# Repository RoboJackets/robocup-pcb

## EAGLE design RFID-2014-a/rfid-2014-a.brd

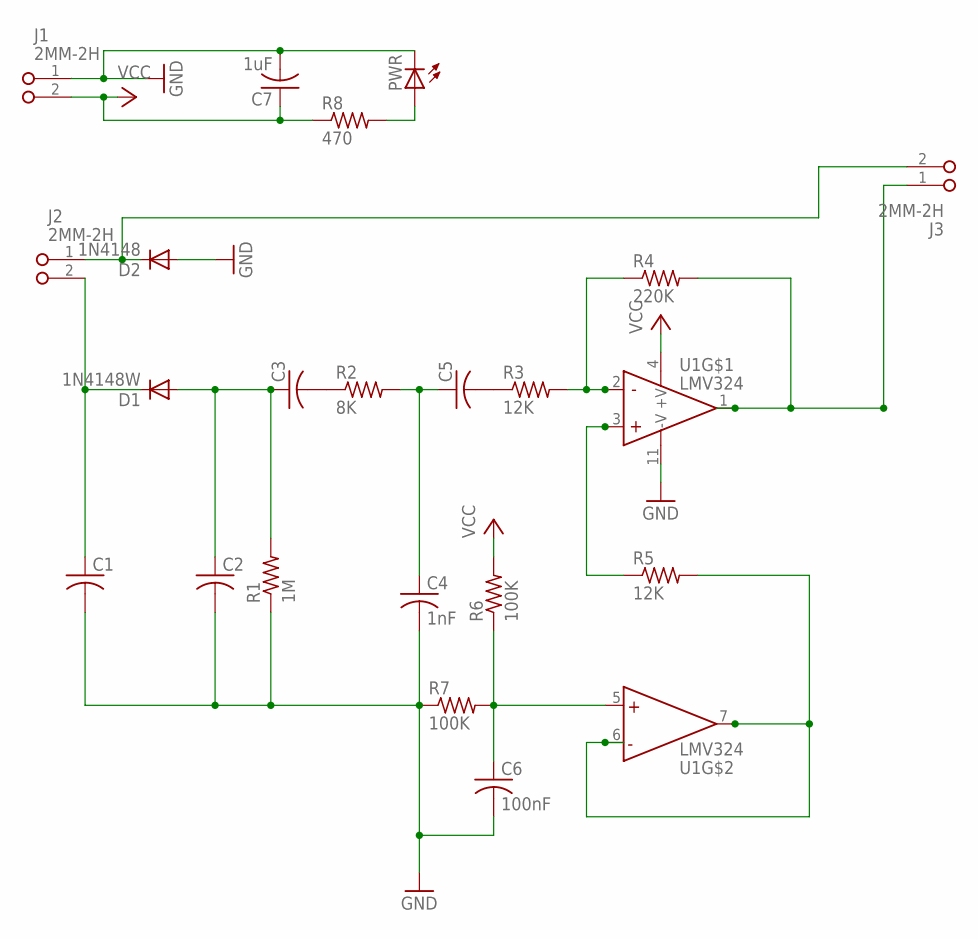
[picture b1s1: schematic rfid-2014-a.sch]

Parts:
C1, C2, C3, C5: C-USC0603; C0603
C4: 1nF; C0603
C6: 100nF; C0603
C7: 1uF; C0603
D1: 1N4148W; SOD123
D2: 1N4148; SOD123
J1, J2, J3: 2MM-2H; 2MM-2-H
PWR: LEDCHIPLED_0603; CHIPLED_0603
R1: 1M; R0603
R2: 8K; R0603
R3, R5: 12K; R0603
R4: 220K; R0603
R6, R7: 100K; R0603
R8: 470; R0603
U1: LMV324; SO014

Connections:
+IN: U1.10 (+IN), U1.12 (+IN)
-IN: U1.9 (-IN), U1.13 (-IN)
GND: C1.2, C2.2, C4.2, C6.2, C7.2, D2.A, J1.1, PWR.C, R1.1, R7.1, U1.11 (-V)
unnamed: R3.2, R4.1, U1.2 (-IN)
unnamed: J3.1, R4.2, U1.1 (OUT)
unnamed: C3.2, R2.1
unnamed: R5.1, U1.3 (+IN)
unnamed: R5.2, U1.6 (-IN), U1.7 (OUT)
unnamed: C5.2, R3.1
unnamed: C6.1, R6.1, R7.2, U1.5 (+IN)
unnamed: C4.1, C5.1, R2.2
unnamed: C1.1, D1.C, J2.2
unnamed: C2.1, C3.1, D1.A, R1.2
unnamed: D2.C, J2.1, J3.2
unnamed: PWR.A, R8.2
OUT: U1.8 (OUT), U1.14 (OUT)
VCC: C7.1, J1.2, R6.2, R8.1, U1.4 (+V)

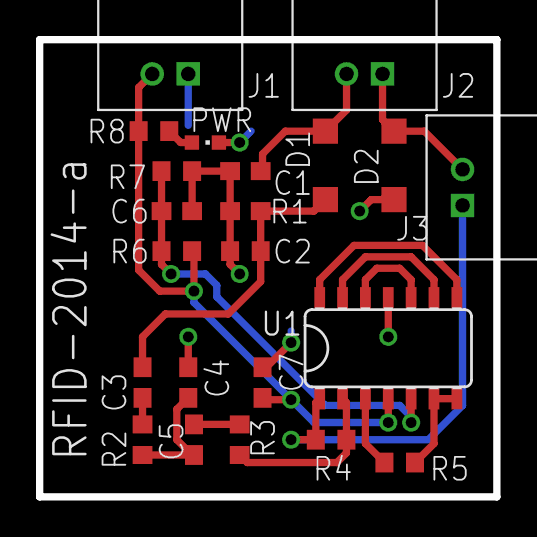
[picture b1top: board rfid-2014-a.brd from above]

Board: 2 copper layers, 25.4 x 25.4 mm, 22 parts (0 on the bottom side), 17 nets.

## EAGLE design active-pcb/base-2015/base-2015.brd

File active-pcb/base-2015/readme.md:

# Radio Board 2015

The 2015 radio has an mbed as the main processor and two radio boards.  We currently only use one of them, but in the future we'd like to support more than six robots at a time.  Two radio boards should give us capacity to communicate with 12 if we implement it in software.

The board also has a mini usb connector, which is used in normal operation.  The mbed's usb port is only needed for flashing new firmware or debugging.  You can use the two usb ports simultaneously.

## PCB

* Radio board connector: "CONN HEADER 10POS .050 VERT SMD"
  * http://www.digikey.com/product-search/en/connectors-interconnects/rectangular-board-to-board-connectors-headers-male-pins/1442672?k=609%203175%20nd

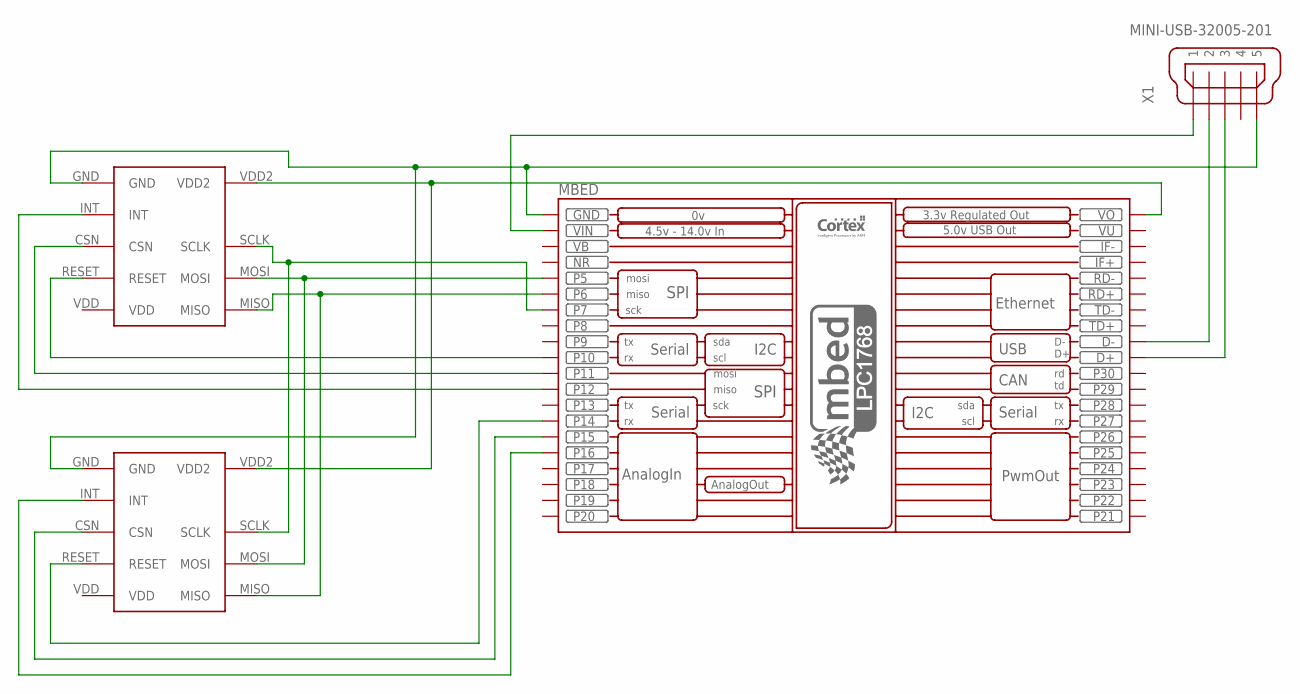
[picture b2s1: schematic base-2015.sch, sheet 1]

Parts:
MBED: MBED_NXP_LPC1768; MBED-KIT
U$1, U$2: RADIOBOARD2015CONNECTOR
X1: MINI-USB-32005-201; 32005-201

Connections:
unnamed: MBED.P$5 (P5), U$1.MOSI, U$2.MOSI
unnamed: MBED.P$6 (P6), U$1.MISO, U$2.MISO
unnamed: MBED.P$15 (P15), U$2.CSN
unnamed: MBED.VIN, X1.1
unnamed: MBED.D-, X1.2
unnamed: MBED.D+, X1.3
unnamed: MBED.VOUT (VO), U$1.VDD2, U$2.VDD2
unnamed: MBED.P$12 (P12), U$1.INT
unnamed: MBED.P$11 (P11), U$1.CSN
unnamed: MBED.P$10 (P10), U$1.RESET
unnamed: MBED.P$16 (P16), U$2.INT
unnamed: MBED.P$14 (P14), U$2.RESET
unnamed: MBED.GND, U$1.GND, U$2.GND, X1.5
unnamed: MBED.P$7 (P7), U$1.SCLK, U$2.SCLK
VB: MBED.VB
VU: MBED.VU

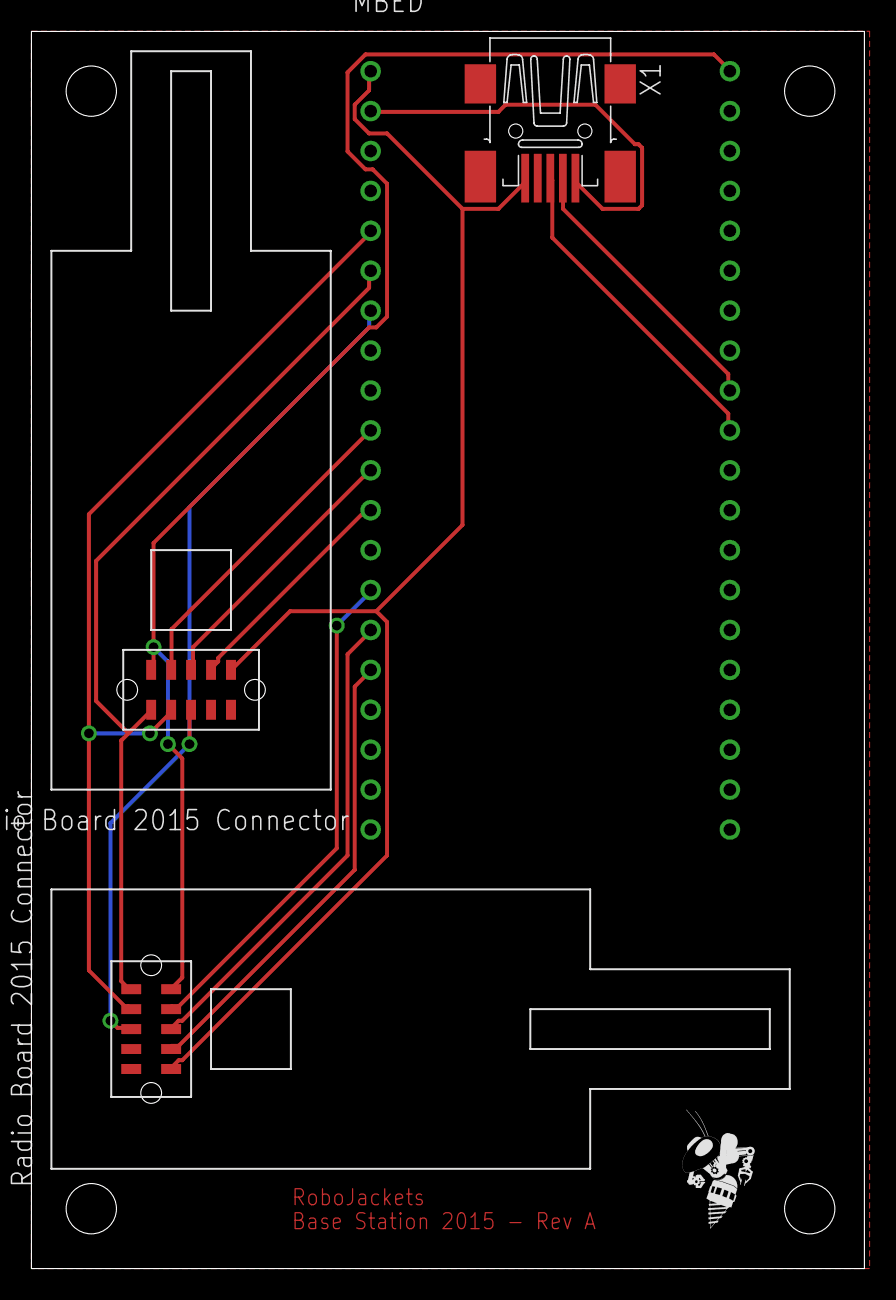
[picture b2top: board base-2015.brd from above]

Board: 2 copper layers, 53.0 x 78.7 mm, 5 parts (0 on the bottom side), 14 nets.

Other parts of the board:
U$3: ROBOBUZZ0.4X; ROBOBUZZ_0.4X

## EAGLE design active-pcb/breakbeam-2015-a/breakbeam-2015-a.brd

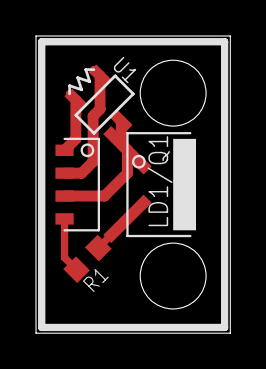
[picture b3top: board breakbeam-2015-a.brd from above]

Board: 2 copper layers, 10.8 x 16.5 mm, 5 parts (0 on the bottom side), 5 nets.

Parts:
LD1/Q1: 2LEAD_H_FACEDOWN_SHORT_MIN
R1: R0603
R3: 0.3k-2.2k; GHOST_0.075
U1: SOT-23-3
U$1: PAD_4

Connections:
+5V: R3.P$2, U1.2, U$1.P$1
GND: LD1/Q1.1, U1.3, U$1.P$3
unnamed: LD1/Q1.2, R1.2
OPTICAL: R1.1, U$1.P$4
SERIAL_ID: R3.P$1, U1.1, U$1.P$2

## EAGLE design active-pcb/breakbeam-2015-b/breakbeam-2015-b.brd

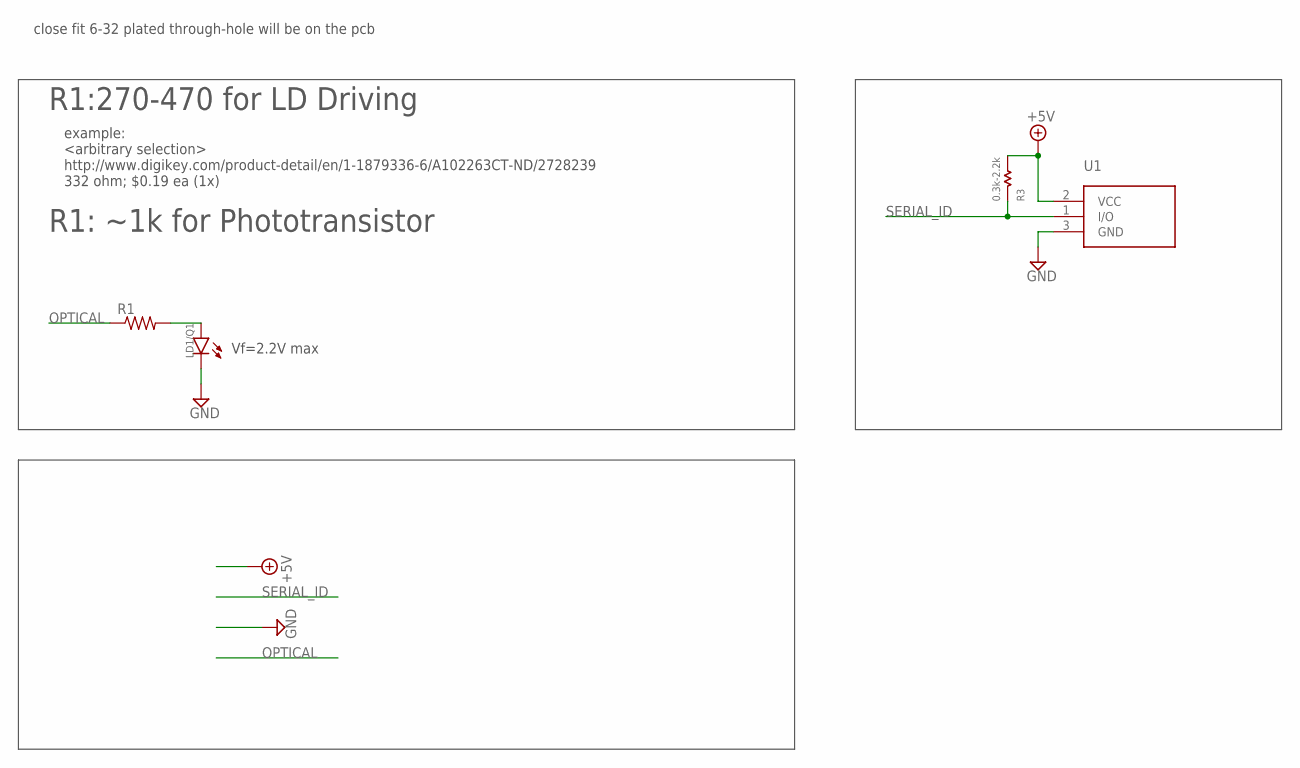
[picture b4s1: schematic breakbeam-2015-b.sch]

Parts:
LD1/Q1: LD_SIDELOOK_FACEDOWNEXTRA_SHORT_LEAD_MINIMIZED; 2LEAD_H_FACEDOWN_XSHORT_MIN
R1: R-US_R0603; R0603
R3: 0.3k-2.2k; GHOST_0.075
U1: DS2411; SOT-23-3

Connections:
+5V: R3.P$2 (PIN2), U1.2 (VCC)
GND: LD1/Q1.1 (C), U1.3 (GND)
unnamed: LD1/Q1.2 (A), R1.2
OPTICAL: R1.1
SERIAL_ID: R3.P$1 (PIN1), U1.1 (I/O)

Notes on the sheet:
Vf=2.2V max
example: <arbitrary selection> http://www.digikey.com/product-detail/en/1-1879336-6/A102263CT-ND/2728239 332 ohm; $0.19 ea (1x)
close fit 6-32 plated through-hole will be on the pcb
R1:270-470 for LD Driving
R1: ~1k for Phototransistor

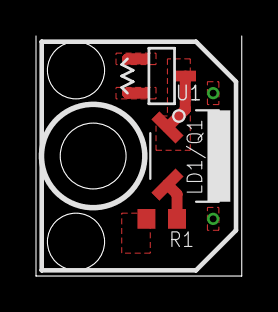
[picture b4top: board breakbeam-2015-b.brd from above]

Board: 2 copper layers, 11.4 x 13.3 mm, 4 parts (0 on the bottom side), 4 nets.

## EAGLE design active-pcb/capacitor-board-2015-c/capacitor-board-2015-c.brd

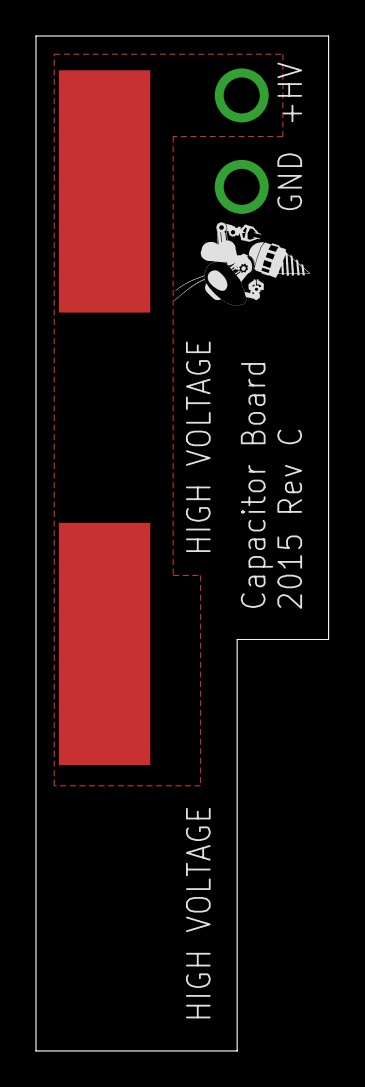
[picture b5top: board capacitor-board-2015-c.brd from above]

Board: 2 copper layers, 16.3 x 56.4 mm, 6 parts (1 on the bottom side), 2 nets, no tracks yet.

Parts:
C1, C2: 25MM-DIA_HORIZ
U$1, U$3: VIA_2MM
U$2, U$4: ROBOBUZZ_0.4X

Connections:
GND: C1.-, C2.-, U$3.P$1
HV: C1.+, C2.+, U$1.P$1

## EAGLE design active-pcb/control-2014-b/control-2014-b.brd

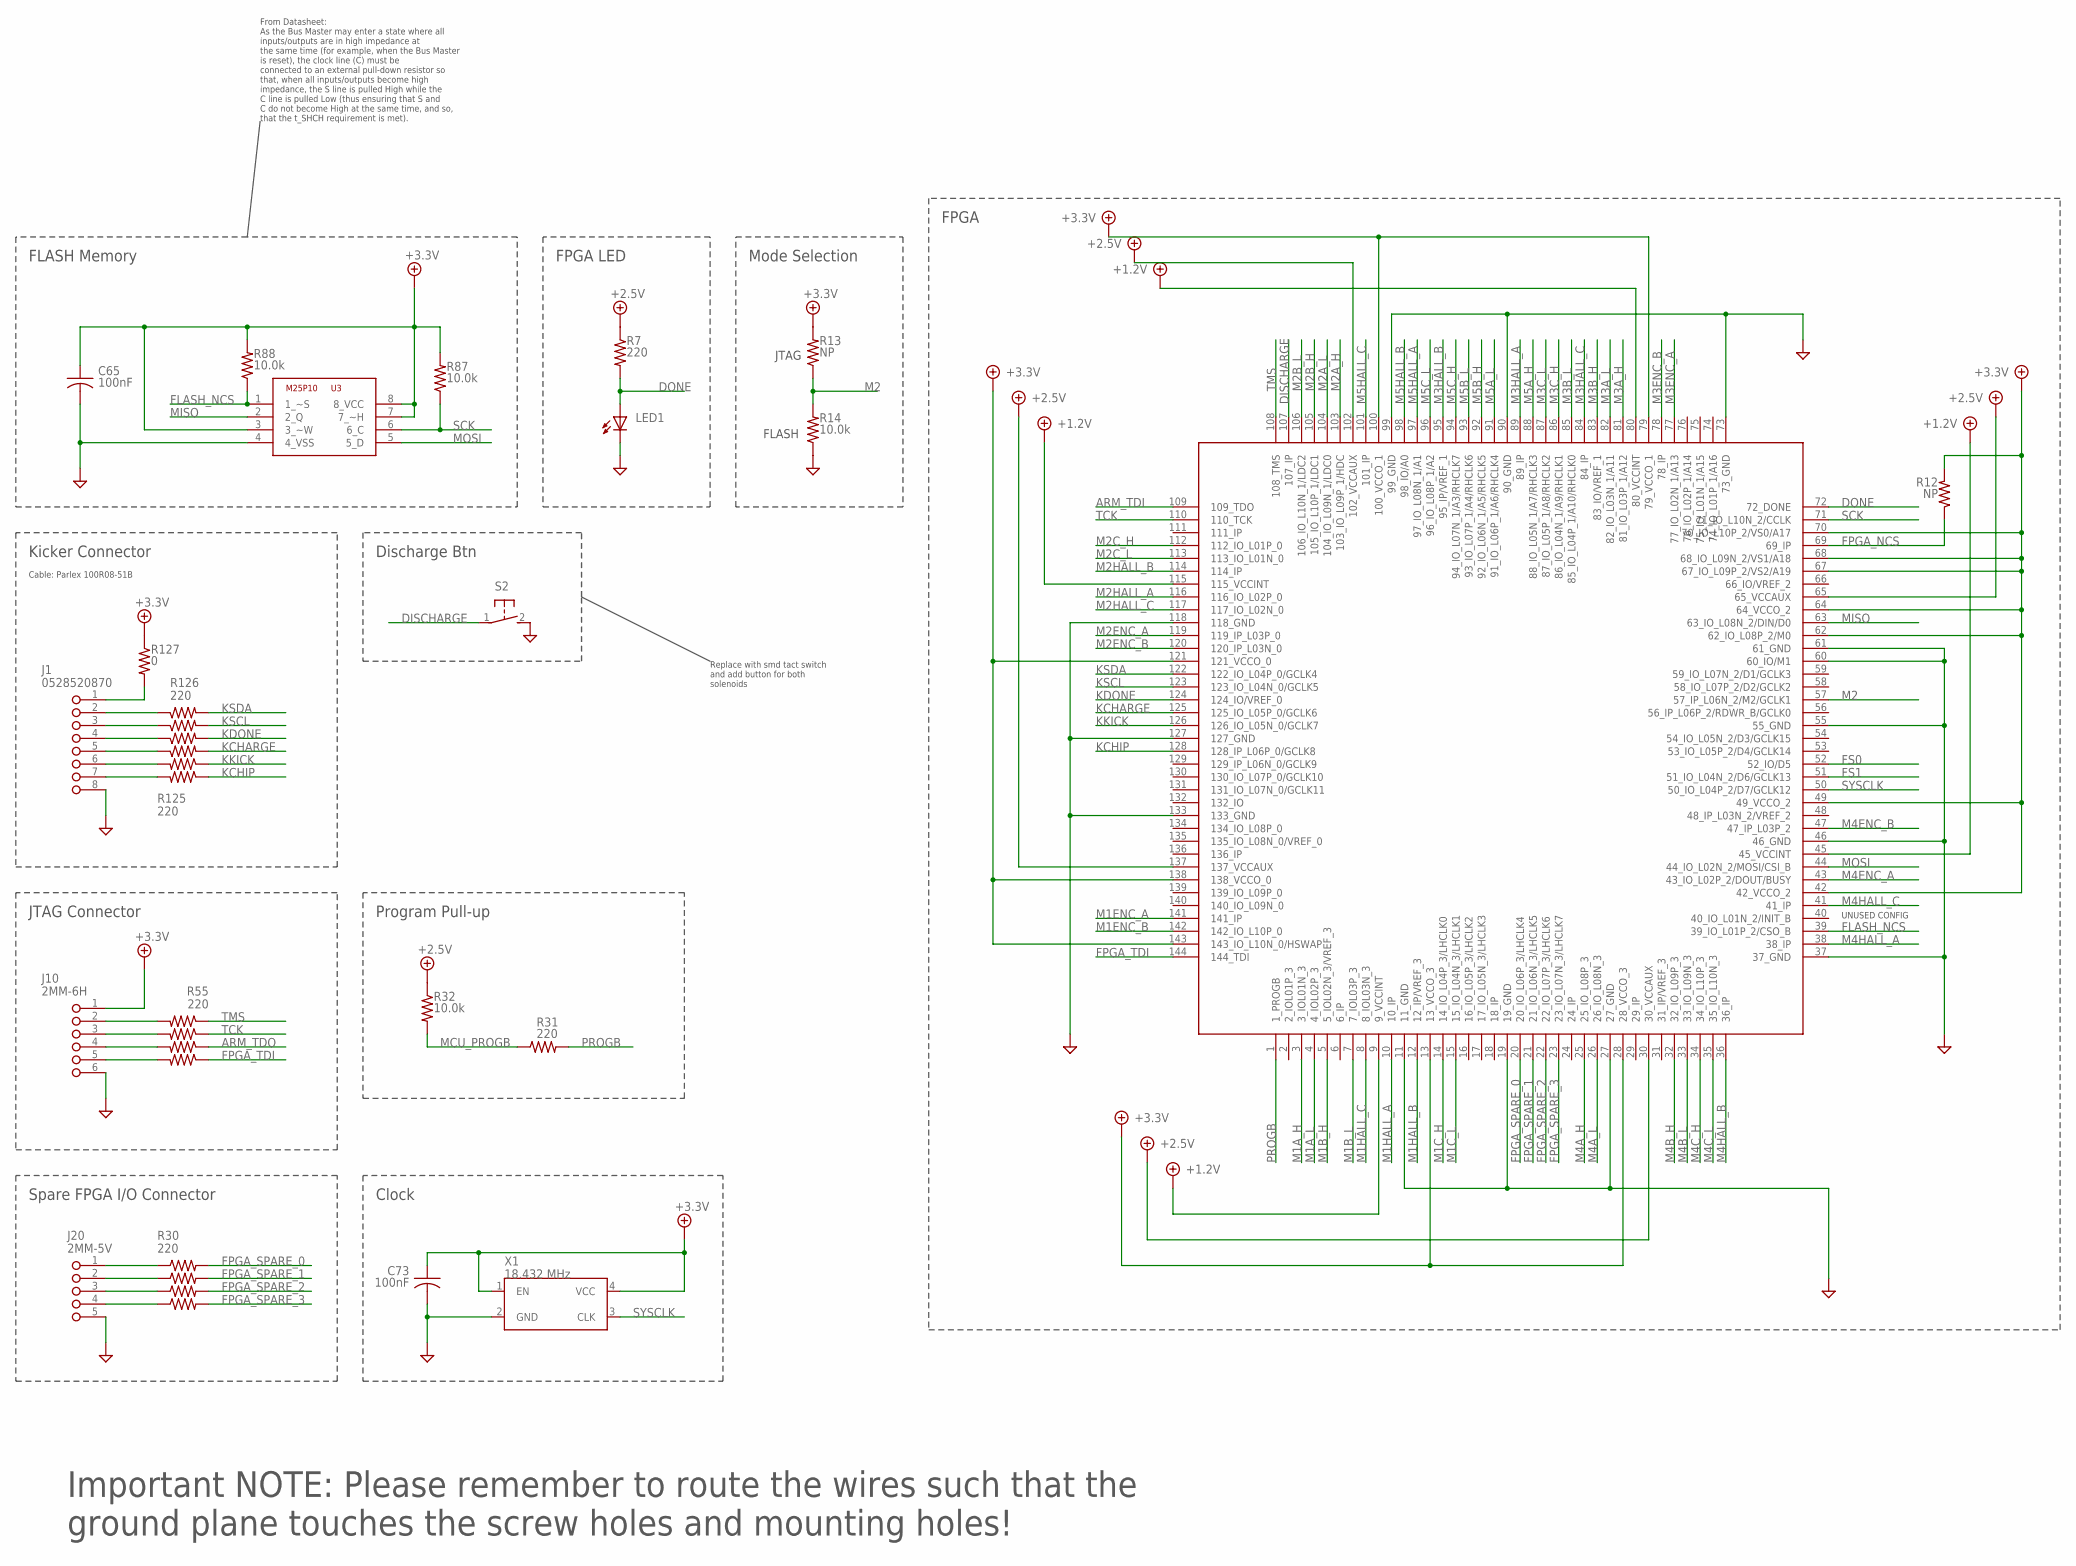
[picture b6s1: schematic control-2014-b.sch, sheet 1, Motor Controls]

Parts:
C65, C73: 100nF; C0603
J1: 0528520870
J10: 2MM-6H; 2MM-6-H
J20: 2MM-5V; 2MM-5-V
LED1: LEDCHIP-LED0603; CHIP-LED0603
R7, R31: 220; R0603
R12, R13: NP; R0603
R14, R32, R87, R88: 10.0k; R0603
R30, R55, R126: 220; RA_4_1206
R125: 220; RA_2_0606
R127: 0; R0603
S2: 31-XX; B3F-31XX
U1: XC3S100E; TQFP144
U3: M25P10; SO08
X1: 18.432 MHz; XTAL_LCC

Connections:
+1.2V: U1.9 (9_VCCINT), U1.45 (45_VCCINT), U1.80 (80_VCCINT), U1.115 (115_VCCINT); also elsewhere on the board
+2.5V: R7.1, R32.1, U1.30 (30_VCCAUX), U1.65 (65_VCCAUX), U1.102 (102_VCCAUX), U1.137 (137_VCCAUX); also elsewhere on the board
+3.3V: C65.1, C73.1, J10.1, R12.2, R13.2, R87.2, R88.2, R127.1, U1.13 (13_VCCO_3), U1.28 (28_VCCO_3), U1.42 (42_VCCO_2), U1.49 (49_VCCO_2), U1.62 (62_IO_L08P_2/M0), U1.64 (64_VCCO_2), U1.67 (67_IO_L09P_2/VS2/A19), U1.68 (68_IO_L09N_2/VS1/A18), U1.70 (70_IO_L10P_2/VS0/A17), U1.79 (79_VCCO_1), U1.100 (100_VCCO_1), U1.121 (121_VCCO_0), U1.138 (138_VCCO_0), U1.143 (143_IO_L10N_0/HSWAP), U3.3 (3_~W), U3.7 (7_~H), U3.8 (8_VCC), X1.1 (EN), X1.4 (VCC); also elsewhere on the board
ARM_TDI: U1.109 (109_TDO); also elsewhere on the board
ARM_TDO: R55.5; also elsewhere on the board
DISCHARGE: S2.1, U1.107 (107_IP)
DONE: LED1.A, R7.2, U1.72 (72_DONE)
FLASH_NCS: R88.1, U1.39 (39_IO_L01P_2/CSO_B), U3.1 (1_~S); also elsewhere on the board
FPGA_NCS: R12.1, U1.69 (69_IP); also elsewhere on the board
FPGA_SPARE_0: R30.2, U1.20 (20_IO_L06P_3/LHCLK4)
FPGA_SPARE_1: R30.4, U1.21 (21_IO_L06N_3/LHCLK5)
FPGA_SPARE_2: R30.6, U1.22 (22_IO_L07P_3/LHCLK6)
FPGA_SPARE_3: R30.8, U1.23 (23_IO_L07N_3/LHCLK7)
FPGA_TDI: R55.7, U1.144 (144_TDI)
FS0: U1.52 (52_IO/D5); also elsewhere on the board
FS1: U1.51 (51_IO_L04N_2/D6/GCLK13); also elsewhere on the board
GND: C65.2, C73.2, J1.8, J10.6, J20.5, LED1.C, R14.1, S2.2 (S), U1.11 (11_GND), U1.19 (19_GND), U1.27 (27_GND), U1.37 (37_GND), U1.46 (46_GND), U1.55 (55_GND), U1.60 (60_IO/M1), U1.61 (61_GND), U1.73 (73_GND), U1.90 (90_GND), U1.99 (99_GND), U1.118 (118_GND), U1.127 (127_GND), U1.133 (133_GND), U3.4 (4_VSS), X1.2 (GND); also elsewhere on the board
KCHARGE: R126.2, U1.125 (125_IO_L05P_0/GCLK6)
KCHIP: R125.3, U1.128 (128_IP_L06P_0/GCLK8)
KDONE: R126.4, U1.124 (124_IO/VREF_0)
KKICK: R125.1, U1.126 (126_IO_L05N_0/GCLK7)
KSCL: R126.6, U1.123 (123_IO_L04N_0/GCLK5)
KSDA: R126.8, U1.122 (122_IO_L04P_0/GCLK4)
M1A_H: U1.3 (3_IOL01N_3); also elsewhere on the board
M1A_L: U1.4 (4_IOL02P_3); also elsewhere on the board
M1B_H: U1.5 (5_IOL02N_3/VREF_3); also elsewhere on the board
M1B_L: U1.7 (7_IOL03P_3); also elsewhere on the board
M1C_H: U1.14 (14_IO_L04P_3/LHCLK0); also elsewhere on the board
M1C_L: U1.15 (15_IO_L04N_3/LHCLK1); also elsewhere on the board
M1ENC_A: U1.141 (141_IP); also elsewhere on the board
M1ENC_B: U1.142 (142_IO_L10P_0); also elsewhere on the board
M1HALL_A: U1.10 (10_IP); also elsewhere on the board
M1HALL_B: U1.12 (12_IP/VREF_3); also elsewhere on the board
M1HALL_C: U1.8 (8_IOL03N_3); also elsewhere on the board
M2: R13.1, R14.2, U1.57 (57_IP_L06N_2/M2/GCLK1)
M2A_H: U1.103 (103_IO_L09P_1/HDC); also elsewhere on the board
M2A_L: U1.104 (104_IO_L09N_1/LDC0); also elsewhere on the board
M2B_H: U1.105 (105_IO_L10P_1/LDC1); also elsewhere on the board
M2B_L: U1.106 (106_IO_L10N_1/LDC2); also elsewhere on the board
M2C_H: U1.112 (112_IO_L01P_0); also elsewhere on the board
M2C_L: U1.113 (113_IO_L01N_0); also elsewhere on the board
M2ENC_A: U1.119 (119_IP_L03P_0); also elsewhere on the board
M2ENC_B: U1.120 (120_IP_L03N_0); also elsewhere on the board
M2HALL_A: U1.116 (116_IO_L02P_0); also elsewhere on the board
M2HALL_B: U1.114 (114_IP); also elsewhere on the board
M2HALL_C: U1.117 (117_IO_L02N_0); also elsewhere on the board
M3A_H: U1.81 (81_IO_L03P_1/A12); also elsewhere on the board
M3A_L: U1.82 (82_IO_L03N_1/A11); also elsewhere on the board
M3B_H: U1.83 (83_IO/VREF_1); also elsewhere on the board
M3B_L: U1.85 (85_IO_L04P_1/A10/RHCLK0); also elsewhere on the board
M3C_H: U1.86 (86_IO_L04N_1/A9/RHCLK1); also elsewhere on the board
M3C_L: U1.87 (87_IO_L05P_1/A8/RHCLK2); also elsewhere on the board
M3ENC_A: U1.77 (77_IO_L02N_1/A13); also elsewhere on the board
M3ENC_B: U1.78 (78_IP); also elsewhere on the board
M3HALL_A: U1.89 (89_IP); also elsewhere on the board
M3HALL_B: U1.95 (95_IP/VREF_1); also elsewhere on the board
M3HALL_C: U1.84 (84_IP); also elsewhere on the board
M4A_H: U1.25 (25_IO_L08P_3); also elsewhere on the board
M4A_L: U1.26 (26_IO_L08N_3); also elsewhere on the board
M4B_H: U1.32 (32_IO_L09P_3); also elsewhere on the board
M4B_L: U1.33 (33_IO_L09N_3); also elsewhere on the board
M4C_H: U1.34 (34_IO_L10P_3); also elsewhere on the board
M4C_L: U1.35 (35_IO_L10N_3); also elsewhere on the board
M4ENC_A: U1.43 (43_IO_L02P_2/DOUT/BUSY); also elsewhere on the board
M4ENC_B: U1.47 (47_IP_L03P_2); also elsewhere on the board
M4HALL_A: U1.38 (38_IP); also elsewhere on the board
M4HALL_B: U1.36 (36_IP); also elsewhere on the board
M4HALL_C: U1.41 (41_IP); also elsewhere on the board
M5A_H: U1.88 (88_IO_L05N_1/A7/RHCLK3); also elsewhere on the board
M5A_L: U1.91 (91_IO_L06P_1/A6/RHCLK4); also elsewhere on the board
M5B_H: U1.92 (92_IO_L06N_1/A5/RHCLK5); also elsewhere on the board
M5B_L: U1.93 (93_IO_L07P_1/A4/RHCLK6); also elsewhere on the board
M5C_H: U1.94 (94_IO_L07N_1/A3/RHCLK7); also elsewhere on the board
M5C_L: U1.96 (96_IO_L08P_1/A2); also elsewhere on the board
M5HALL_A: U1.97 (97_IO_L08N_1/A1); also elsewhere on the board
M5HALL_B: U1.98 (98_IO/A0); also elsewhere on the board
M5HALL_C: U1.101 (101_IP); also elsewhere on the board
MCU_PROGB: R31.1, R32.2; also elsewhere on the board
MISO: U1.63 (63_IO_L08N_2/DIN/D0), U3.2 (2_Q); also elsewhere on the board
MOSI: U1.44 (44_IO_L02N_2/MOSI/CSI_B), U3.5 (5_D); also elsewhere on the board
unnamed: J10.3, R55.4
unnamed: J10.5, R55.8
unnamed: J1.2, R126.7
unnamed: J1.3, R126.5
unnamed: J1.4, R126.3
unnamed: J1.5, R126.1
unnamed: J10.4, R55.6
unnamed: J10.2, R55.2
unnamed: J1.6, R125.2
unnamed: J1.7, R125.4
unnamed: J1.1, R127.2
unnamed: J20.3, R30.5
unnamed: J20.2, R30.3
unnamed: J20.1, R30.1
unnamed: J20.4, R30.7
PROGB: R31.2, U1.1 (1_PROGB)
SCK: R87.1, U1.71 (71_IO_L10N_2/CCLK), U3.6 (6_C); also elsewhere on the board
SYSCLK: U1.50 (50_IO_L04P_2/D7/GCLK12), X1.3 (CLK); also elsewhere on the board
TCK: R55.3, U1.110 (110_TCK); also elsewhere on the board
TMS: R55.1, U1.108 (108_TMS); also elsewhere on the board

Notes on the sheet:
JTAG
FLASH
UNUSED CONFIG
Cable: Parlex 100R08-51B
Important NOTE: Please remember to route the wires such that the ground plane touches the screw holes and mounting holes!
JTAG Connector
Clock
Kicker Connector
Mode Selection
Discharge Btn
Program Pull-up
FLASH Memory
FPGA LED
FPGA
Spare FPGA I/O Connector
Replace with smd tact switch and add button for both solenoids
From Datasheet: As the Bus Master may enter a state where all inputs/outputs are in high impedance at the same time (for example, when the Bus Master is reset), the clock line (C) must be connected to an external pull-down resistor so that, when all inputs/outputs become high impedance, the S line 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

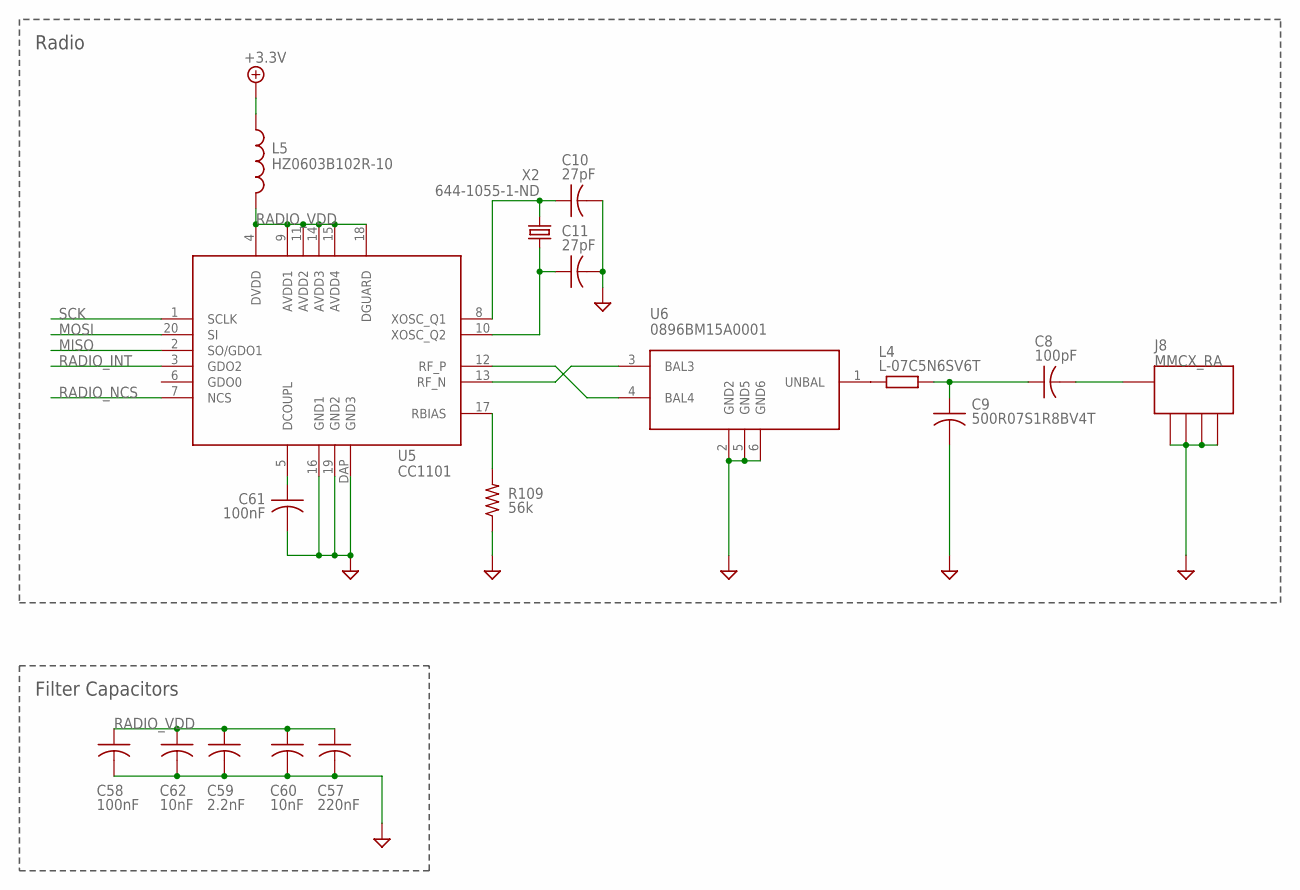
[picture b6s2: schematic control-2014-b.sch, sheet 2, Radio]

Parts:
C8: 100pF; C0603
C9: 500R07S1R8BV4T; C0402
C10, C11: 27pF; C0603
C57: 220nF; C0603
C58, C61: 100nF; C0603
C59: 2.2nF; C0603
C60, C62: 10nF; C0603
J8: MMCX_RA
L4: L-07C5N6SV6T; R0402
L5: HZ0603B102R-10; C0603
R109: 56k; R0603
U5: CC1101; QLP20
U6: 0896BM15A0001
X2: 644-1055-1-ND; XTAL-3.2X2.5

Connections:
+3.3V: L5.1; also elsewhere on the board
GND: C9.2, C10.2, C11.2, C57.2, C58.2, C59.2, C60.2, C61.2, C62.2, J8.P$2, J8.P$3, J8.P$4, J8.P$5, R109.1, U5.16 (GND1), U5.19 (GND2), U5.DAP (GND3), U6.2 (GND2), U6.5 (GND5), U6.6 (GND6); also elsewhere on the board
MISO: U5.2 (SO/GDO1); also elsewhere on the board
MOSI: U5.20 (SI); also elsewhere on the board
unnamed: C61.1, U5.5 (DCOUPL)
unnamed: R109.2, U5.17 (RBIAS)
unnamed: C11.1, U5.10 (XOSC_Q2), X2.1
unnamed: C10.1, U5.8 (XOSC_Q1), X2.3 (2)
unnamed: L4.1, U6.1 (UNBAL)
unnamed: C8.1, C9.1, L4.2
unnamed: U5.12 (RF_P), U6.4 (BAL4)
unnamed: U5.13 (RF_N), U6.3 (BAL3)
unnamed: C8.2, J8.P$1
RADIO_INT: U5.3 (GDO2); also elsewhere on the board
RADIO_NCS: U5.7 (NCS); also elsewhere on the board
RADIO_VDD: C57.1, C58.1, C59.1, C60.1, C62.1, L5.2, U5.4 (DVDD), U5.9 (AVDD1), U5.11 (AVDD2), U5.14 (AVDD3), U5.15 (AVDD4), U5.18 (DGUARD)
SCK: U5.1 (SCLK); also elsewhere on the board

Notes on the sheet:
Radio
Filter Capacitors

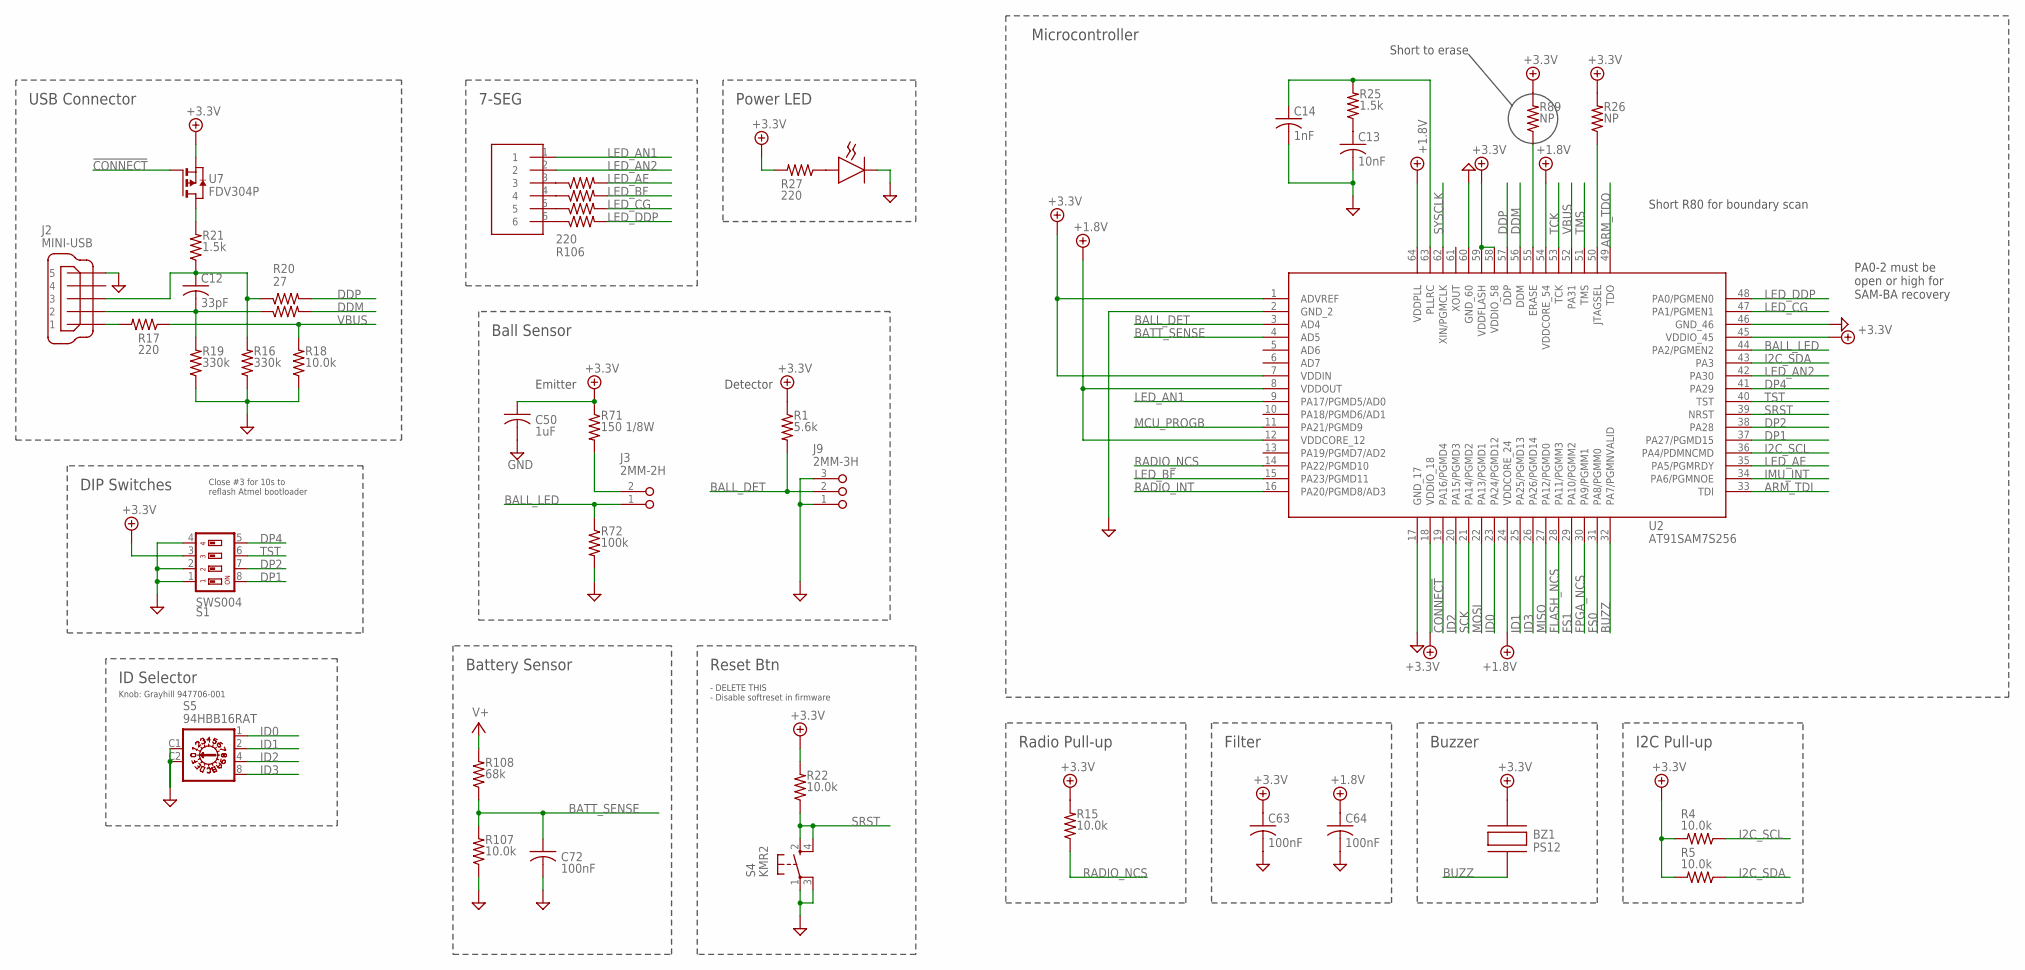
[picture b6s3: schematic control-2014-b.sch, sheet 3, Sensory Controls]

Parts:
BZ1: PS12
C12: 33pF; C0603
C13: 10nF; C0603
C14: 1nF; C0603
C50: 1uF; C0603
C63, C64, C72: 100nF; C0603
J2: MINI-USB; UX60A-MB-5ST
J3: 2MM-2H; 2MM-2-H
J9: 2MM-3H; 2MM-3-H
LED2: LED2; 5350T5
LED3: LDS-M514RI-RA
R1: 5.6k; R0603
R4, R5, R15, R18, R22, R107: 10.0k; R0603
R16, R19: 330k; R0603
R17, R27: 220; R0603
R20: 27; RA_2_0606
R21, R25: 1.5k; R0603
R26, R89: NP; R0603
R71: 150 1/8W; R0805
R72: 100k; R0603
R106: 220; RA_4_1206
R108: 68k; R0603
S1: SWS004; SMS-004
S4: KMR2
S5: 94HBB16RAT; HEX-RA-2C
U2: AT91SAM7S256; SQFP-S-10X10-64
U7: FDV304P; SOT-23

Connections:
!CONNECT: U2.19 (PA16/PGMD4), U7.3 (G)
+1.8V: C64.1, U2.8 (VDDOUT), U2.12 (VDDCORE_12), U2.24 (VDDCORE_24), U2.54 (VDDCORE_54), U2.64 (VDDPLL); also elsewhere on the board
+3.3V: BZ1.2, C50.1, C63.1, R1.1, R4.2, R5.2, R15.2, R22.2, R26.2, R27.2, R71.1, R89.2, S1.3, U2.1 (ADVREF), U2.7 (VDDIN), U2.18 (VDDIO_18), U2.45 (VDDIO_45), U2.58 (VDDIO_58), U2.59 (VDDFLASH), U7.2 (S); also elsewhere on the board
ARM_TDI: U2.33 (TDI); also elsewhere on the board
ARM_TDO: U2.49 (TDO); also elsewhere on the board
BALL_DET: J9.2, R1.2, U2.3 (AD4)
BALL_LED: J3.1, R72.1, U2.44 (PA2/PGMEN2)
BATT_SENSE: C72.1, R107.2, R108.1, U2.4 (AD5)
BUZZ: BZ1.1, U2.32 (PA7/PGMNVALID)
DDM: R20.2, U2.56 (DDM)
DDP: R20.4, U2.57 (DDP)
DP1: S1.8, U2.37 (PA27/PGMD15)
DP2: S1.7, U2.38 (PA28)
DP4: S1.5, U2.41 (PA29)
FLASH_NCS: U2.28 (PA11/PGMM3); also elsewhere on the board
FPGA_NCS: U2.30 (PA9/PGMM1); also elsewhere on the board
FS0: U2.31 (PA8/PGMM0); also elsewhere on the board
FS1: U2.29 (PA10/PGMM2); also elsewhere on the board
GND: C13.2, C14.2, C50.2, C63.2, C64.2, C72.2, J2.5, J9.1, J9.3, LED2.CATHODE (2), R16.1, R18.1, R19.1, R72.2, R107.1, S1.1, S1.2, S1.4, S4.1, S4.3, S5.C1, S5.C2, U2.2 (GND_2), U2.17 (GND_17), U2.46 (GND_46), U2.60 (GND_60); also elsewhere on the board
I2C_SCL: R4.1, U2.36 (PA4/PDMNCMD); also elsewhere on the board
I2C_SDA: R5.1, U2.43 (PA3); also elsewhere on the board
ID0: S5.1, U2.23 (PA24/PGMD12)
ID1: S5.2, U2.25 (PA25/PGMD13)
ID2: S5.4, U2.20 (PA15/PGMD3)
ID3: S5.8, U2.26 (PA26/PGMD14)
IMU_INT: U2.34 (PA6/PGMNOE); also elsewhere on the board
LED_AE: R106.8, U2.35 (PA5/PGMRDY)
LED_AN1: LED3.1, U2.9 (PA17/PGMD5/AD0)
LED_AN2: LED3.2, U2.42 (PA30)
LED_BF: R106.6, U2.15 (PA23/PGMD11)
LED_CG: R106.4, U2.47 (PA1/PGMEN1)
LED_DDP: R106.2, U2.48 (PA0/PGMEN0)
MCU_PROGB: U2.11 (PA21/PGMD9); also elsewhere on the board
MISO: U2.27 (PA12/PGMD0); also elsewhere on the board
MOSI: U2.22 (PA13/PGMD1); also elsewhere on the board
unnamed: LED3.6, R106.1
unnamed: LED3.5, R106.3
unnamed: LED3.4, R106.5
unnamed: LED3.3, R106.7
unnamed: LED2.ANODE (1), R27.1
unnamed: J3.2, R71.2
unnamed: R26.1, U2.50 (JTAGSEL)
unnamed: C12.2, J2.2, R19.2, R20.1
unnamed: R89.1, U2.55 (ERASE)
unnamed: C12.1, J2.3, R16.2, R20.3, R21.1
unnamed: R21.2, U7.1 (D)
unnamed: C13.1, R25.1
unnamed: C14.1, R25.2, U2.63 (PLLRC)
unnamed: J2.1, R17.2
RADIO_INT: U2.16 (PA20/PGMD8/AD3); also elsewhere on the board
RADIO_NCS: R15.1, U2.14 (PA22/PGMD10); also elsewhere on the board
SCK: U2.21 (PA14/PGMD2); also elsewhere on the board
SRST: R22.1, S4.2, S4.4, U2.39 (NRST)
SYSCLK: U2.62 (XIN/PGMCLK); also elsewhere on the board
TCK: U2.53 (TCK); also elsewhere on the board
TMS: U2.51 (TMS); also elsewhere on the board
TST: S1.6, U2.40 (TST)
V+: R108.2; also elsewhere on the board
VBUS: R17.1, R18.2, U2.52 (PA31)

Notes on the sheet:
Emitter
Detector
PA0-2 must be open or high for SAM-BA recovery
Close #3 for 10s to reflash Atmel bootloader
Short to erase
Short R80 for boundary scan
Knob: Grayhill 947706-001
- DELETE THIS - Disable softreset in firmware
USB Connector
Microcontroller
Radio Pull-up
DIP Switches
ID Selector
Battery Sensor
I2C Pull-up
Ball Sensor
Filter
Buzzer
Power LED
7-SEG
Reset Btn

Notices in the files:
parts and their libraries:
SparkFun-AnalogIC: Licensing: CC v3.0 Share-Alike You are welcome to use this library for commercial purposes.
